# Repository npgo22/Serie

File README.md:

# Serie
Serie is a basic mainboard built to handle:
1. Insanely high temperatures
2. Insanely high speeds
3. Several axis of movement

The board itself is based around an STM32H723, the fastest microcontroller supported by Klipper at the moment.

## I/O
Currently, the following I/O is planned:

### Temperature sensing
Four MAX31856 (for type-k thermocouples) modules will be integrated for temperature sensing to be used as follows:
1. Hotend
2. Bed
3. Chamber
4. Spare/standby

Several other standard thermistor inputs will be broken out as needed.

### Motors
There will be 6x motors driven by TMC2241s. Each TMC2241 Support to klipper will need to be added to support this.

### Isolated Inputs
There are 16 digitally isolated inputs.

### Low Power Outputs
There are 6 outputs driven by small MOSFETs for outputs to other devices.

### Buses
As many buses should be broken out as possible.

### 12V Outputs
There are four 12V outputs to drive peripherals such as fans.

### USB
There will be at least 1 USB-C input.

### Ethernet
As I have ethernet stuff on hand, this board will have ethernet.

### Piezo Inputs
There will be a transimpedance amplifier followed by an instrumentation amplifier and an external comparator for piezo measurement. This is because the beacon probe cannot handle higher temperatures.

### Endstops
The enstops will utilize optoisolated inputs, and will be 3 pins to accomodate hall effect sensors.

## Power
As of right now, it is planned to require an external 48V power supply for the motors and a 12V power supply for the mainboard. This maintains galvanic isolation while providing decent protection against  A small switching regulator will generate 5V (AP62300TWU-7 + ETQP4M3R3KVK) which will then be fed into a 2112K-3.3.

### Heaters
Bed and chamber will be mains-powered, and motors will see 48V to 60V. and all the fans will maintain 12V, and the hotend heater cartridge will be able to handle 24V but will require a separate power supply just for it.

#### Switching
Mains powered items will be driven by an SSR, which necessitates the selection of a decent gate driver.

### Motors
Motors will be powered by a separate 48V power supply as they are extremely noisy.

## Board construction
Probably 4 layers. Don't really need more at this time.

## Misc.
* Consider a standardized header for breaking out to other boards.
* Total BoM cost for 2x is expected to be in the neighborhood of $150 once it's all assembled.

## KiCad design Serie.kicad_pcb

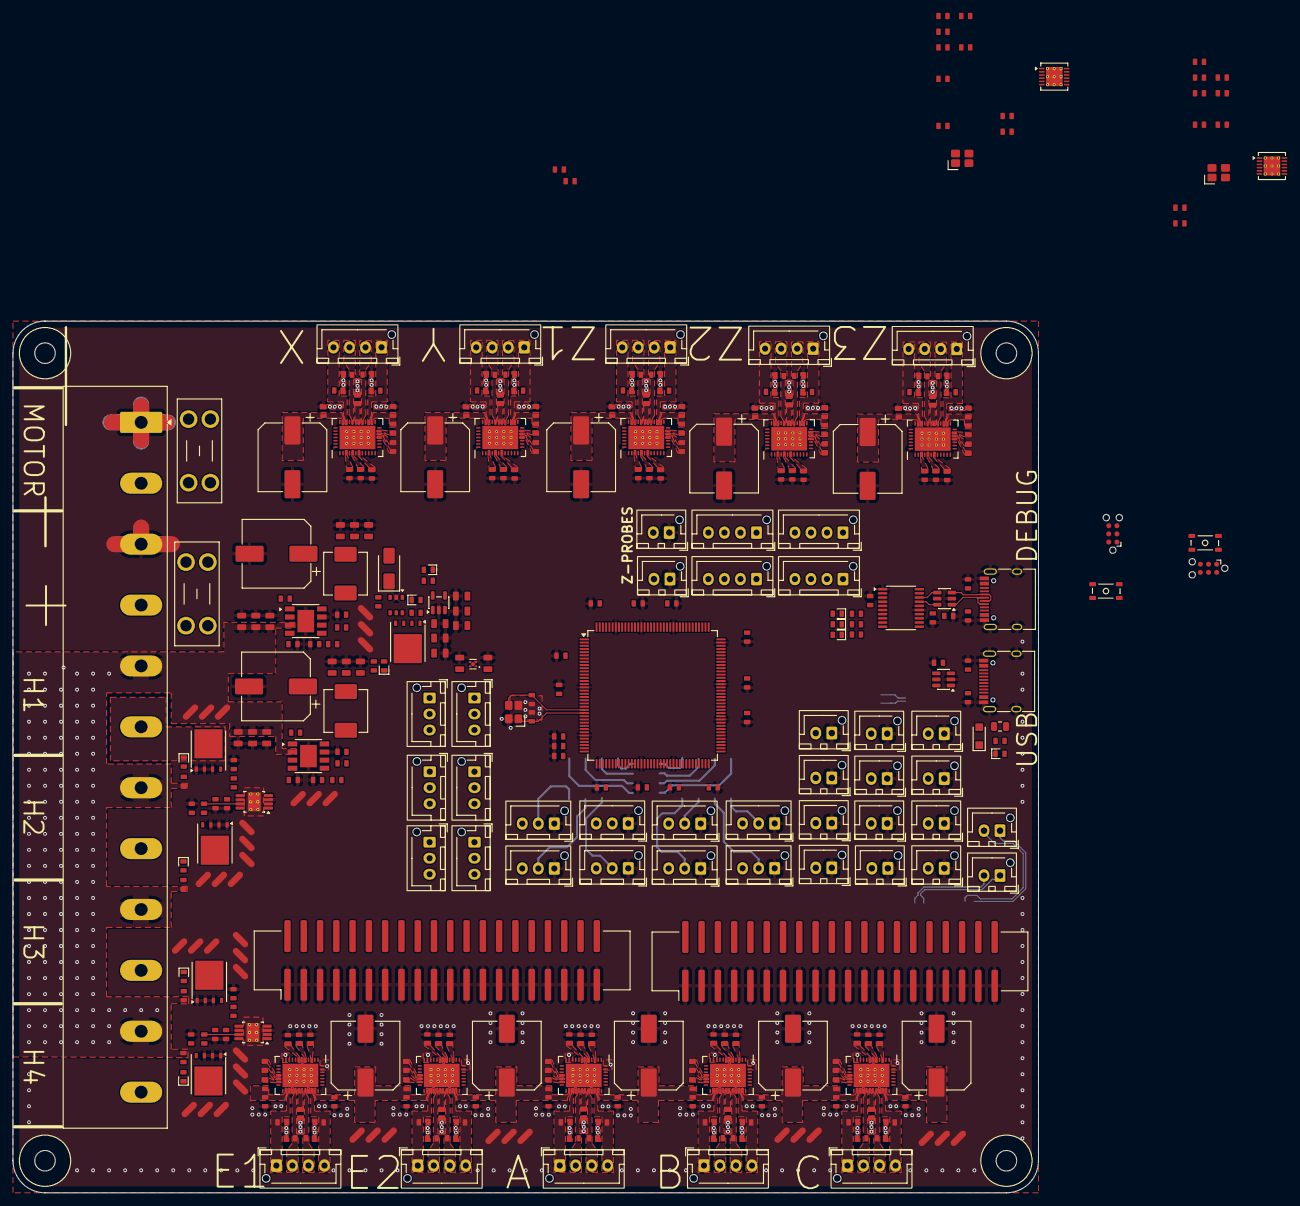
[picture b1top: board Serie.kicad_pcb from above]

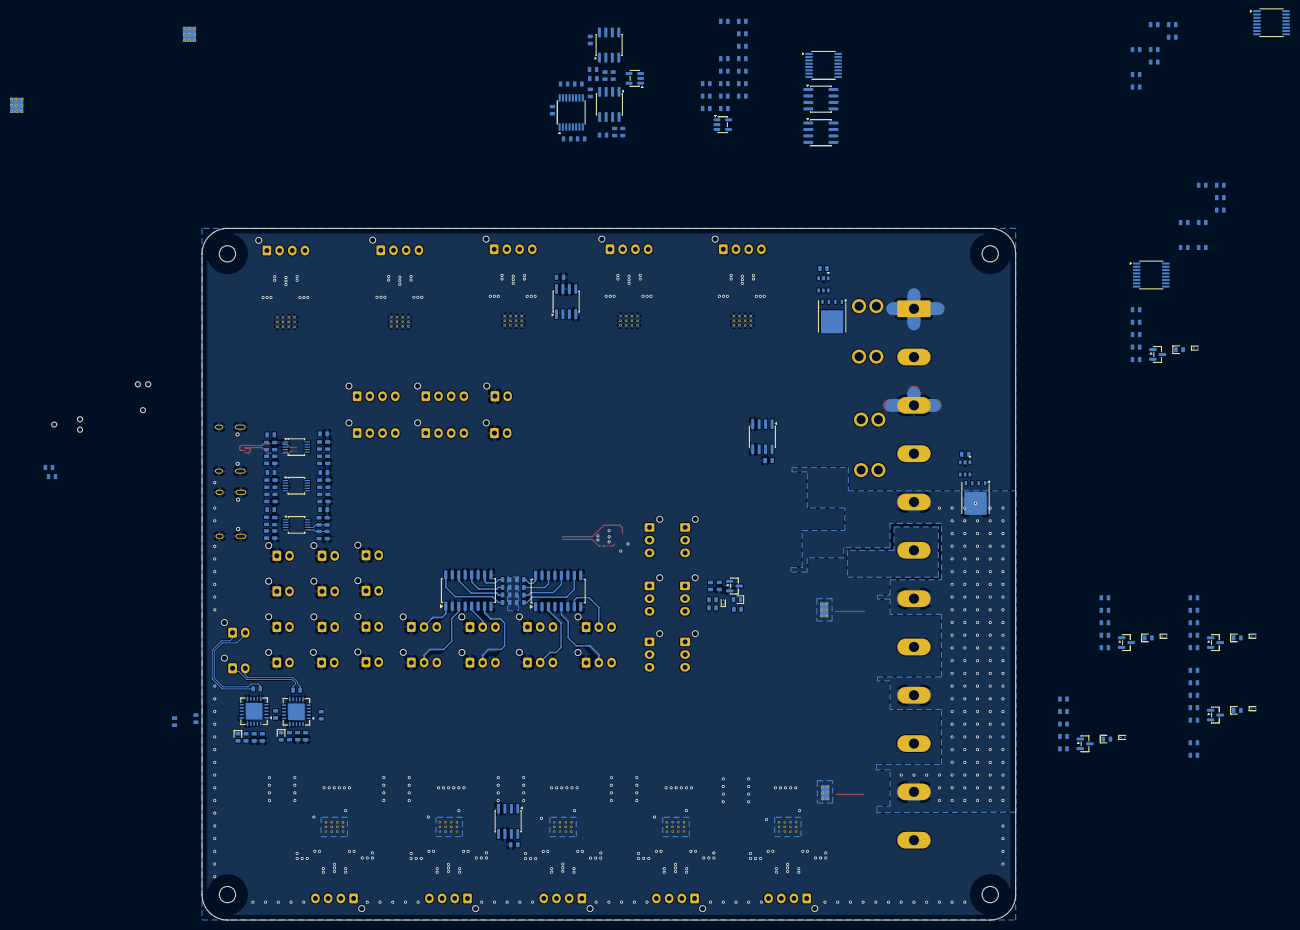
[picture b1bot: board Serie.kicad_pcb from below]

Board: 6 copper layers, 160.0 x 136.0 mm, 518 parts (179 on the bottom side), 303 nets.

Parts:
C1, C2: 10pF; C_0603
C3, C4, C93, C105, C117, C129, C141, C153, C184, C214, C226, C238: 2.2uF; C_0603
C5, C6, C7, C9, C12, C13, C14, C18, C19, C20, C21, C22, C24, C25, C26, C27, C28, C36, C38, C46, C56, C58, C59, C60, C61, C62, C63, C64, C65, C66, C67, C68, C69, C70, C71, C72, C74, C76, C77, C79, C80, C84, C85, C86, C92, C96, C97, C98, C104, C108, C109, C110, C116, C120, C121, C122, C128, C132, C133, C134, C140, C144, C145, C146, C152, C154, C155, C156, C158, C161, C162, C163, C167, C168, C169, C170, C171, C175, C176, C177, C183, C185, C186, C187, C188, C189, C191, C192, C193, C194, C195, C197, C198, C199, C200, C201, C205, C206, C207, C213, C217, C218, C219, C225, C229, C230, C231, C237: 100nF; C_0603
C8, C11, C78, C81, C157, C160: 10nF; C_0603
C10, C159: 10uF; C_0603
C15, C16, C164, C165: ?uF; C_0603
C17, C166: 100pF; C_0603
C23, C172: 30pF; C_0603
C29, C30, C31, C33, C34, C35, C39, C40, C41, C43, C44, C45, C48, C49, C50, C51, C52, C53, C54, C55: 22uF; C_0805
C32, C42, C87, C99, C111, C123, C135, C147, C178, C208, C220, C232: 100uF; CP_Elec_10x10.5
C37, C47: 1nF; C_0603
C57, C73, C75: 1uF; C_0603
C82, C83, C94, C95, C106, C107, C118, C119, C130, C131, C142, C143, C173, C174, C203, C204, C215, C216, C227, C228: 22nF; C_0603
C88, C89, C90, C91, C100, C101, C102, C103, C112, C113, C114, C115, C124, C125, C126, C127, C136, C137, C138, C139, C148, C149, C150, C151, C179, C180, C181, C182, C209, C210, C211, C212, C221, C222, C223, C224, C233, C234, C235, C236: 470pF; C_0603
C190, C196, C202: 100n; C_0603
D1: PMEG3010BER; Nexperia_CFP3_SOD-123W
D2, D3, D4, D5, D6, D8, D9, D10, D11, D12, D13, D14, D16, D18, D22, D24, D26: LED_Small; LED_0603
D7: SS54; D_SMA
D15, D17, D19, D23, D25, D27: ESD9B3.3ST5G; D_SOD-923
D20, D21: LED; LED_0603
F1: 500mA; Fuse_0805_2012Metric
F2, F3: XF-508P-B-B; Fuseholder_Blade_Mini_Keystone_3568
H1, H2, H3, H4: MountingHole; MountingHole_3.2mm_M3
J1, J2: Conn_02x20_Counter_Clockwise; IDC-Header_2x20_P2.54mm_Vertical_SMD
J3, J9: Conn_ARM_SWD_TagConnect_TC2030-NL; Tag-Connect_TC2030-IDC-NL_2x03_P1.27mm_Vertical
J4, J5, J24, J25, J26, J27, J28, J29, J30, J31, J33, J46, J47, J48: Conn_01x04; JST_XH_B4B-XH-AM_1x04_P2.50mm_Vertical
J6, J22, J23, J32, J34, J35, J36, J37, J38, J39, J40, J41, J42, J43, J44, J45: Conn_01x02; JST_XH_B2B-XH-AM_1x02_P2.50mm_Vertical
J7, J8: USB_C_Receptacle_USB2.0_16P; USB_C_Receptacle_HRO_TYPE-C-31-M-12
J10: Screw_Terminal_06x01x02; TerminalBlock_Ningbo-Kagnex_HB9500M_1x12_P9.5mm
J11, J12, J13, J14, J15, J16, J17, J18, J19, J20, J21, J49, J50, J51: Conn_01x03; JST_XH_B3B-XH-AM_1x03_P2.50mm_Vertical
L1: 6.8 uH; L_Changjiang_FXL0630
L2: 3.3 uH; L_Changjiang_FXL0630
Q1, Q2, Q3, Q4, Q5, Q6, Q7: BSC016N06NS; TDSON-8-1
Q8, Q9, Q10, Q11, Q12, Q13: AO3400A; SOT-23
R1, R2, R81, R82: 100R; R_0603
R3, R4, R5, R6, R7, R8, R9, R10, R16, R17, R21, R22, R48, R53, R58, R83, R84, R85, R86, R87, R88, R89, R90, R96, R97, R98, R99, R103, R104, R105, R106, R108, R109, R110, R111, R118, R123, R128: 4.7k; R_0603
R11, R36, R39, R42, R45, R50, R55, R60, R91, R120, R125, R130: 100k; R_0603
R12, R92: 10M; R_0603
R13, R14, R15, R18, R19, R20, R23, R25, R28, R31, R33, R34, R37, R40, R43, R46, R47, R51, R52, R56, R57, R61, R62, R63, R64, R65, R66, R67, R68, R69, R70, R72, R73, R93, R94, R100, R101, R102, R107, R112, R116, R117, R121, R122, R126, R127: 10k; R_0603
R24: 140k; R_0603
R26, R30: 200k; R_0603
R27, R32: 30.9k; R_0603
R29: 52.5k; R_0603
R35, R38, R41, R44, R49, R54, R59, R119, R124, R129: 10R; R_0603
R71, R74: 4.02k; R_0603
R75, R76, R77, R78, R79, R80, R95, R113, R114, R115: 24k; R_0603
SW1, SW2: SKRPANE010
U1: STM32H723ZGT6; LQFP-144_20x20mm_P0.5mm
U2, U30: ADS1220xPW; TSSOP-16_4.4x5mm_P0.65mm
U3, U31: TMUX1108PW; TSSOP-16_4.4x5mm_P0.65mm
U4, U5, U32, U33: TLV6742; SOIC-8_3.9x4.9mm_P1.27mm
U6, U34: LDC1612; WSON-12-1EP_4x4mm_P0.5mm_EP2.6x3mm_ThermalVias
U7, U35: TMUX1101DBV; SOT-23-5
U8, U10: USBLC6-2SC6; SOT-23-6
U9: STM32F042F4Px; TSSOP-20_4.4x6.5mm_P0.65mm
U11, U13: AP64500; Diodes_SO-8EP
U12, U14, U17: AP74700Q; SOT-6
U15: TLV77533; SOT-23-5
U16: TPS7A20xxxDQN; Texas_X2SON-4_1x1mm_P0.65mm
U18, U19: UCC27524DGN; Texas_DGN0008G_VSSOP-8-1EP_3x3mm_P0.65mm_EP2x2.94mm_Mask1.8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
U20, U21: LTV-247; SOP-16_4.4x10.4mm_P1.27mm
U22, U23: MAX31865xTP; TQFN-20-1EP_5x5mm_P0.65mm_EP3.25x3.25mm
U24, U25, U26, U27, U28, U29, U36, U43, U44, U45: TMC2241ATC; QFN-38_EP_5.63x7.6_Pitch0.5mm
U37, U39, U42: ADS1115IDGS; TSSOP-10_3x3mm_P0.5mm
U38, U40, U41: LM75B; SOIC-8_3.9x4.9mm_P1.27mm
Y1: 25 MHz; 3225-4P-L
Y2, Y3: 12 MHz; 3225-4P-L

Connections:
+3.3V: C5.2, C7.2, C12.2, C13.2, C14.1, C22.1, C24.1, C25.1, C51.2, C52.2, C53.2, C57.2, C58.2, C59.2, C60.2, C61.2, C62.2, C63.2, C64.2, C65.2, C66.2, C67.2, C68.2, C69.2, C70.2, C71.2, C76.1, C77.1, C79.1, C80.1, C92.2, C104.2, C116.2, C128.2, C140.2, C152.2, C154.2, C156.2, C161.2, C162.2, C163.1, C171.1, C183.2, C185.1, C186.1, C191.1, C192.1, C197.1, C198.1, C213.2, C225.2, C237.2, D3.2 (A), D4.2 (A), D5.2 (A), J3.1 (VCC), J9.1 (VCC), J14.3, J15.3, J16.3, J17.3, J18.3, J19.3, J20.3, J21.3, R13.1, R33.1, R46.1, R51.1, R56.1, R61.1, R62.1, R63.1, R64.1, R65.1, R66.1, R67.1, R68.1, R69.1, R70.1, R72.1, R73.1, R93.1, R96.1, R97.1, R98.1, R99.1, R100.2, R101.2, R102.2, R103.1, R104.1, R105.1, R106.1, R107.2, R108.1, R109.1, R110.1, R111.1, R112.2, R116.1, R121.1, R126.1, U1.6 (VBAT), U1.17 (VDD), U1.30 (VDD), U1.32 (VREF+), U1.33 (VDDA), U1.39 (VDD), U1.52 (VDD), U1.62 (VDD), U1.72 (VDD), U1.84 (VDD), U1.95 (VDD33USB), U1.108 (VDD), U1.121 (VDD), U1.131 (VDD), U1.143 (PDR_ON), U1.144 (VDD), U2.13 (DVDD), U3.2 (EN), U3.13 (VDD), U4.8 (V+), U5.8 (V+), U6.7 (VDD), U7.5 (V_{DD}), U9.5 (VDDA), U9.16 (VDD), U15.5 (VOUT), U22.19 (DVDD), U22.20 (VDD), U23.19 (DVDD), U23.20 (VDD), U24.7 (VCCIO), U24.33 (~SLEEP), U25.7 (VCCIO), U25.33 (~SLEEP), U26.7 (VCCIO), U26.33 (~SLEEP), U27.7 (VCCIO), U27.33 (~SLEEP), U28.7 (VCCIO), U28.33 (~SLEEP), U29.7 (VCCIO), U29.33 (~SLEEP), U30.13 (DVDD), U31.2 (EN), U31.13 (VDD), U32.8 (V+), U33.8 (V+), U34.7 (VDD), U35.5 (V_{DD}), U36.7 (VCCIO), U36.33 (~SLEEP), U37.8 (VDD), U38.6 (A1), U38.7 (A0), U38.8 (+Vs), U39.1 (ADDR), U39.8 (VDD), U40.5 (A2), U40.8 (+Vs), U41.5 (A2), U41.7 (A0), U41.8 (+Vs), U42.8 (VDD), U43.7 (VCCIO), U43.33 (~SLEEP), U44.7 (VCCIO), U44.33 (~SLEEP), U45.7 (VCCIO), U45.33 (~SLEEP), Y2.4 (V+), Y3.4 (V+)
+4.5V: C6.1, C10.1, C55.1, C155.1, C159.1, J4.4, J30.4, U2.11 (AIN0/REFP1), U2.12 (AVDD), U16.1 (OUT), U30.11 (AIN0/REFP1), U30.12 (AVDD)
+5V: C48.2, C49.2, C50.2, C54.1, D1.1 (K), Q2.5 (D), U14.4 (CATHODE), U15.1 (VIN), U15.3 (EN), U16.3 (EN), U16.4 (IN)
+12V: C32.1, C33.1, C34.1, C35.1, C72.2, C73.2, C74.2, C75.2, J11.1, J12.1, J13.1, J49.1, J50.1, J51.1, L1.2, R23.1, R24.1, R47.1, R52.1, R57.1, R117.1, R122.1, R127.1, U18.1 (ENA), U18.6 (V_{DD}), U18.8 (ENB), U19.1 (ENA), U19.6 (V_{DD}), U19.8 (ENB)
+24V: C29.1, C30.1, C31.1, C39.1, C40.1, C41.1, J10.5 (Pin_1), J10.7 (Pin_1), J10.9 (Pin_1), J10.11 (Pin_1), Q1.5 (D), R34.1, R37.1, R40.1, R43.1, U11.2 (VIN), U11.3 (EN), U12.4 (CATHODE), U13.2 (VIN), U13.3 (EN)
/Connections/Debugger and USB/IF_SWCLK: J9.4 (SWCLK), U9.20 (PA14)
/Connections/Debugger and USB/IF_SWDIO: J9.2 (SWDIO), U9.19 (PA13)
/Connections/Debugger and USB/USB_CONN_D+: J7.A6 (D+), J7.B6 (D+), J8.A6 (D+), J8.B6 (D+), U8.3 (I/O2), U10.3 (I/O2)
/Connections/Debugger and USB/USB_CONN_D-: J7.A7 (D-), J7.B7 (D-), J8.A7 (D-), J8.B7 (D-), U8.1 (I/O1), U10.1 (I/O1)
/Connections/Debugger and USB/USB_D+: U9.18 (PA10/PA12), U10.4 (I/O2)
/Connections/Debugger and USB/USB_D-: U9.17 (PA9/PA11), U10.6 (I/O1)
/Connections/Debugger and USB/~RST: J9.3 (~RESET), SW2.3 (K), SW2.4 (A), U9.4 (NRST)
/Connections/High Power Outputs 1/OUTA: R35.1, U18.5 (OUTB)
/Connections/High Power Outputs 1/OUTB: R38.1, U18.7 (OUTA)
/Connections/High Power Outputs 2/OUTA: R41.1, U19.5 (OUTB)
/Connections/High Power Outputs 2/OUTB: R44.1, U19.7 (OUTA)
/Connections/IN1: R61.2, U20.16
/Connections/IN2: R62.2, U20.14
/Connections/IN3: R63.2, U20.12
/Connections/IN4: R64.2, U20.10
/Connections/IN5: R65.2, U21.16
/Connections/IN6: R66.2, U21.14
/Connections/IN7: R67.2, U21.12
/Connections/IN8: R68.2, U21.10
/Connections/Low Power Outputs/TACH1: D15.2 (A2), R46.2, R48.2
/Connections/Low Power Outputs/TACH2: D17.2 (A2), R51.2, R53.2
/Connections/Low Power Outputs/TACH3: D19.2 (A2), R56.2, R58.2
/Connections/Low Power Outputs/TACH4: D23.2 (A2), R116.2, R118.2
/Connections/Low Power Outputs/TACH5: D25.2 (A2), R121.2, R123.2
/Connections/Low Power Outputs/TACH6: D27.2 (A2), R126.2, R128.2
/Connections/SWCLK: J3.4 (SWCLK), U1.109 (PA14(JTCK), U9.12 (PA6)
/Connections/SWDIO: J3.2 (SWDIO), U1.105 (PA13(JTMS), U9.11 (PA5)
/Connections/Sensors 1/CLK: C23.1, U6.3 (CLKIN), Y2.3 (OUT)
/Connections/Sensors 1/PIEZO: U5.6 (-), U5.7
/Connections/Sensors 1/vref: U3.8 (D), U4.3 (+), U4.7
/Connections/Sensors 2/CLK: C172.1, U34.3 (CLKIN), Y3.3 (OUT)
/Connections/Sensors 2/PIEZO: U33.6 (-), U33.7
/Connections/Sensors 2/vref: U31.8 (D), U32.3 (+), U32.7
/Connections/Thermistors/SCL: R101.1, U37.10 (SCL), U38.2 (SCL), U39.10 (SCL), U40.2 (SCL), U41.2 (SCL), U42.10 (SCL)
/Connections/Thermistors/SDA: R102.1, U37.9 (SDA), U38.1 (SDA), U39.9 (SDA), U40.1 (SDA), U41.1 (SDA), U42.1 (ADDR), U42.9 (SDA)
/Connections/Thermistors/TS_ALRT/RDY_1: R100.1, U37.2 (ALERT/RDY)
/Connections/Thermistors/TS_ALRT/RDY_2: R107.1, U39.2 (ALERT/RDY)
/Connections/Thermistors/TS_ALRT/RDY_3: R112.1, U42.2 (ALERT/RDY)
/Connections/Thermocouple 1/T1+: C78.1, J22.2, U22.5 (FORCE+), U22.7 (RTDIN+)
/Connections/Thermocouple 1/T1-: C78.2, J22.1, U22.8 (RTDIN-), U22.9 (FORCE-)
/Connections/Thermocouple 2/T1+: C81.1, J23.2, U23.5 (FORCE+), U23.7 (RTDIN+)
/Connections/Thermocouple 2/T1-: C81.2, J23.1, U23.8 (RTDIN-), U23.9 (FORCE-)
/Connections/~RST: J3.3 (~RESET), SW1.1, SW1.2, U1.25 (NRST), U9.14 (PB1)
/Connections/~TC_CS_1: R70.2, U22.13 (~CS)
/Connections/~TC_CS_2: R73.2, U23.13 (~CS)
DRV_MISO: U24.37 (SDO/NAO), U25.37 (SDO/NAO), U26.37 (SDO/NAO), U27.37 (SDO/NAO), U28.37 (SDO/NAO), U29.37 (SDO/NAO), U36.37 (SDO/NAO), U43.37 (SDO/NAO), U44.37 (SDO/NAO), U45.37 (SDO/NAO)
DRV_MOSI: U24.36 (SDI/AD0), U25.36 (SDI/AD0), U26.36 (SDI/AD0), U27.36 (SDI/AD0), U28.36 (SDI/AD0), U29.36 (SDI/AD0), U36.36 (SDI/AD0), U43.36 (SDI/AD0), U44.36 (SDI/AD0), U45.36 (SDI/AD0)
DRV_SCK: U24.35 (SCK/AD1), U25.35 (SCK/AD1), U26.35 (SCK/AD1), U27.35 (SCK/AD1), U28.35 (SCK/AD1), U29.35 (SCK/AD1), U36.35 (SCK/AD1), U43.35 (SCK/AD1), U44.35 (SCK/AD1), U45.35 (SCK/AD1)
GND: C1.1, C2.1, C3.1, C4.1, C5.1, C6.2, C7.1, C8.1, C11.2, C12.1, C13.1, C14.2, C18.1, C19.1, C20.1, C21.1, C22.2, C23.2, C24.2, C25.2, C26.2, C27.2, C29.2, C30.2, C31.2, C32.2, C33.2, C34.2, C35.2, C37.2, C39.2, C40.2, C41.2, C42.2, C43.2, C44.2, C45.2, C47.2, C48.1, C49.1, C50.1, C51.1, C52.1, C53.1, C54.2, C55.2, C57.1, C58.1, C59.1, C60.1, C61.1, C62.1, C63.1, C64.1, C65.1, C66.1, C67.1, C68.1, C69.1, C70.1, C71.1, C72.1, C73.1, C74.1, C75.1, C76.2, C77.2, C79.2, C80.2, C84.2, C85.2, C86.2, C87.2, C88.2, C89.2, C90.2, C91.2, C92.1, C93.1, C96.2, C97.2, C98.2, C99.2, C100.2, C101.2, C102.2, C103.2, C104.1, C105.1, C108.2, C109.2, C110.2, C111.2, C112.2, C113.2, C114.2, C115.2, C116.1, C117.1, C120.2, C121.2, C122.2, C123.2, C124.2, C125.2, C126.2, C127.2, C128.1, C129.1, C132.2, C133.2, C134.2, C135.2, C136.2, C137.2, C138.2, C139.2, C140.1, C141.1, C144.2, C145.2, C146.2, C147.2, C148.2, C149.2, C150.2, C151.2, C152.1, C153.1, C154.1, C155.2, C156.1, C157.1, C160.2, C161.1, C162.1, C163.2, C167.1, C168.1, C169.1, C170.1, C171.2, C172.2, C175.2, C176.2, C177.2, C178.2, C179.2, C180.2, C181.2, C182.2, C183.1, C184.1, C185.2, C186.2, C187.1, C188.1, C189.1, C190.1, C191.2, C192.2, C193.1, C194.1, C195.1, C196.1, C197.2, C198.2, C199.1, C200.1, C201.1, C202.1, C205.2, C206.2, C207.2, C208.2, C209.2, C210.2, C211.2, C212.2, C213.1, C214.1, C217.2, C218.2, C219.2, C220.2, C221.2, C222.2, C223.2, C224.2, C225.1, C226.1, C229.2, C230.2, C231.2, C232.2, C233.2, C234.2, C235.2, C236.2, C237.1, C238.1, D2.1 (K), D6.1 (K), D8.1 (K), D9.1 (K), D15.1 (A1), D17.1 (A1), D19.1 (A1), D23.1 (A1), D25.1 (A1), D27.1 (A1), J1.1, J1.3, J1.5, J1.7, J1.9, J1.11, J1.13, J1.15, J1.17, J1.19, J1.21, J1.23, J1.25, J1.27, J1.29, J1.31, J1.33, J1.35, J1.37, J1.39, J2.1, J2.3, J2.5, J2.7, J2.9, J2.11, J2.13, J2.15, J2.17, J2.19, J2.21, J2.23, J2.25, J2.27, J2.29, J2.31, J2.33, J2.35, J2.37, J2.39, J3.5 (GND), J6.1, J7.A1 (GND), J7.A12 (GND), J7.B1 (GND), J7.B12 (GND), J7.S1 (SHIELD), J8.A1 (GND), J8.A12 (GND), J8.B1 (GND), J8.B12 (GND), J8.S1 (SHIELD), J9.5 (GND), J10.1, J10.3 (Pin_1), J14.1, J15.1, J16.1, J17.1, J18.1, J19.1, J20.1, J21.1, J32.1, J34.1, J35.1, J36.1, J37.1, J38.1, J39.1, J40.1, J41.1, J42.1, J43.1, J44.1, J45.1, Q4.1 (S), Q4.2 (S), Q4.3 (S), Q5.1 (S), Q5.2 (S), Q5.3 (S), Q6.1 (S), Q6.2 (S), Q6.3 (S), Q7.1 (S), Q7.2 (S), Q7.3 (S), Q8.2 (S), Q9.2 (S), Q10.2 (S), Q11.2 (S), Q12.2 (S), Q13.2 (S), R14.1, R16.1, R17.2, R21.1, R22.2, R25.2, R26.2, R30.2, R31.2, R36.1, R39.1, R42.1, R45.1, R50.1, R55.1, R60.1, R75.2, R76.2, R77.2, R78.2, R79.2, R80.2, R94.1, R95.2, R113.2, R114.2, R115.2, R120.1, R125.1, R130.1, SW1.3 (K), SW1.4 (A), SW2.1, SW2.2, U1.16 (VSS), U1.31 (VSSA), U1.38 (VSS), U1.51 (VSS), U1.61 (VSS), U1.83 (VSS), U1.94 (VSS), U1.107 (VSS), U1.120 (VSS), U1.130 (VSS), U1.138 (BOOT0), U2.3 (CLK), U2.4 (DGND), U2.5 (AVSS), U3.3 (VSS), U3.14 (GND), U4.4 (V-), U4.5 (+), U5.4 (V-), U6.4 (ADDR), U6.6 (SD), U6.8 (GND), U6.13 (GND), U7.2, U7.3 (GND), U8.2 (GND), U9.1 (PB8), U9.15 (VSSA), U10.2 (GND), U11.7 (GND), U11.9 (EP), U12.2 (GND), U13.7 (GND), U13.9 (EP), U14.2 (GND), U15.2 (GND), U16.2 (GND), U16.5 (Pad), U17.2 (GND), U18.3 (GND), U18.9 (GND), U19.3 (GND), U19.9 (GND), U20.2, U20.4, U20.6, U20.8, U20.9, U20.11, U20.13, U20.15, U21.2, U21.4, U21.6, U21.8, U21.9, U21.11, U21.13, U21.15, U22.6 (FORCE2), U22.10 (GND), U22.15 (DGND), U22.16 (GND), U22.21 (GND), U23.6 (FORCE2), U23.10 (GND), U23.15 (DGND), U23.16 (GND), U23.21 (GND), U24.6 (AGND), U24.11 (DRV_EN), U24.23 (PGND), U24.28 (PGND), U24.38 (CLK), U24.39 (EP), U25.6 (AGND), U25.11 (DRV_EN), U25.23 (PGND), U25.28 (PGND), U25.38 (CLK), U25.39 (EP), U26.6 (AGND), U26.11 (DRV_EN), U26.23 (PGND), U26.28 (PGND), U26.38 (CLK), U26.39 (EP), U27.6 (AGND), U27.11 (DRV_EN), U27.23 (PGND), U27.28 (PGND), U27.38 (CLK), U27.39 (EP), U28.6 (AGND), U28.11 (DRV_EN), U28.23 (PGND), U28.28 (PGND), U28.38 (CLK), U28.39 (EP), U29.6 (AGND), U29.11 (DRV_EN), U29.23 (PGND), U29.28 (PGND), U29.38 (CLK), U29.39 (EP), U30.3 (CLK), U30.4 (DGND), U30.5 (AVSS), U31.3 (VSS), U31.14 (GND), U32.4 (V-), U32.5 (+), U33.4 (V-), U34.4 (ADDR), U34.6 (SD), U34.8 (GND), U34.13 (GND), U35.2, U35.3 (GND), U36.6 (AGND), U36.11 (DRV_EN), U36.23 (PGND), U36.28 (PGND), U36.38 (CLK), U36.39 (EP), U37.1 (ADDR), U37.3 (GND), U38.4 (GND), U38.5 (A2), U39.3 (GND), U40.4 (GND), U40.6 (A1), U40.7 (A0), U41.4 (GND), U41.6 (A1), U42.3 (GND), U43.6 (AGND), U43.11 (DRV_EN), U43.23 (PGND), U43.28 (PGND), U43.38 (CLK), U43.39 (EP), U44.6 (AGND), U44.11 (DRV_EN), U44.23 (PGND), U44.28 (PGND), U44.38 (CLK), U44.39 (EP), U45.6 (AGND), U45.11 (DRV_EN), U45.23 (PGND), U45.28 (PGND), U45.38 (CLK), U45.39 (EP), Y1.2 (G), Y1.4 (G), Y2.2 (GND), Y3.2 (GND)
MCU_USB_D+: U1.104 (PA12), U8.4 (I/O2)
MCU_USB_D-: U1.103 (PA11), U8.6 (I/O1)
unnamed: C3.2, U1.71 (VCAP)
unnamed: C4.2, U1.106 (VCAP)
unnamed: C37.1, R27.2
unnamed: C47.1, R32.2
unnamed: D1.2 (A), F1.2, R15.1
unnamed: D2.2 (A), R15.2
unnamed: D3.1 (K), R18.1
unnamed: D4.1 (K), R19.1
unnamed: D5.1 (K), R20.1
unnamed: D6.2 (A), R23.2
unnamed: C42.1, C43.1, C44.1, C45.1, D7.2 (A), L2.2
unnamed: C46.2, D7.1 (K), Q2.1 (S), Q2.2 (S), Q2.3 (S), R28.1, R29.1, U14.3 (EN), U14.6 (ANODE)
unnamed: D8.2 (A), R28.2
unnamed: D9.2 (A), R33.2
unnamed: D10.2 (A), R34.2
unnamed: D10.1 (K), J10.6 (Pin_2), Q4.5 (D)
unnamed: D11.2 (A), R37.2
unnamed: D11.1 (K), J10.8 (Pin_2), Q5.5 (D)
unnamed: D12.2 (A), R40.2
unnamed: D12.1 (K), J10.10 (Pin_2), Q6.5 (D)
unnamed: D13.2 (A), R43.2
unnamed: D13.1 (K), J10.12 (Pin_2), Q7.5 (D)
unnamed: D14.2 (A), R47.2
unnamed: D14.1 (K), J11.2, Q8.3 (D)
unnamed: D16.2 (A), R52.2
unnamed: D16.1 (K), J12.2, Q9.3 (D)
unnamed: D18.2 (A), R57.2
unnamed: D18.1 (K), J13.2, Q10.3 (D)
unnamed: D20.2 (A), R69.2
unnamed: D20.1 (K), U22.18 (~DRDY)
unnamed: D21.2 (A), R72.2
unnamed: D21.1 (K), U23.18 (~DRDY)
unnamed: D22.2 (A), R117.2
unnamed: D22.1 (K), J49.2, Q11.3 (D)
unnamed: D24.2 (A), R122.2
unnamed: D24.1 (K), J50.2, Q12.3 (D)
unnamed: D26.2 (A), R127.2
unnamed: D26.1 (K), J51.2, Q13.3 (D)
unnamed: F2.1, Q1.1 (S), Q1.2 (S), Q1.3 (S)
unnamed: C10.2, J4.1, U2.6 (AIN3/REFN1)
unnamed: J4.2, R2.1
unnamed: J4.3, R1.1
unnamed: C16.1, C21.2, J5.1, U6.12 (IN1B)
unnamed: C16.2, C20.2, J5.2, U6.11 (IN1A)
unnamed: C15.1, C19.2, J5.3, U6.10 (IN0B)
unnamed: C15.2, C18.2, J5.4, U6.9 (IN0A)
unnamed: C17.1, J6.2, R12.1, U4.2 (-), U7.1
unnamed: J7.A5 (CC1), R17.1
unnamed: J7.B5 (CC2), R16.2
unnamed: J8.A5 (CC1), R22.1
unnamed: J8.B5 (CC2), R21.2
unnamed: F3.2, J10.2
unnamed: C36.2, F2.2, J10.4 (Pin_2), U12.3 (EN), U12.6 (ANODE)
unnamed: J11.3, R48.1
unnamed: J12.3, R53.1
unnamed: J13.3, R58.1
unnamed: J14.2, U20.1
unnamed: J15.2, U20.3
unnamed: J16.2, U20.5
unnamed: J17.2, U20.7
unnamed: J18.2, U21.1
unnamed: J19.2, U21.3
unnamed: J20.2, U21.5
unnamed: J21.2, U21.7
unnamed: C91.1, J24.1, U24.22 (OUT1B)
unnamed: C90.1, J24.2, U24.24 (OUT2B)
unnamed: C88.1, J24.3, U24.27 (OUT2A)
unnamed: C89.1, J24.4, U24.29 (OUT1A)
unnamed: C103.1, J25.1, U25.22 (OUT1B)
unnamed: C102.1, J25.2, U25.24 (OUT2B)
unnamed: C100.1, J25.3, U25.27 (OUT2A)
unnamed: C101.1, J25.4, U25.29 (OUT1A)
unnamed: C115.1, J26.1, U26.22 (OUT1B)
unnamed: C114.1, J26.2, U26.24 (OUT2B)
unnamed: C112.1, J26.3, U26.27 (OUT2A)
unnamed: C113.1, J26.4, U26.29 (OUT1A)
unnamed: C127.1, J27.1, U27.22 (OUT1B)
unnamed: C126.1, J27.2, U27.24 (OUT2B)
unnamed: C124.1, J27.3, U27.27 (OUT2A)
unnamed: C125.1, J27.4, U27.29 (OUT1A)
unnamed: C139.1, J28.1, U28.22 (OUT1B)
unnamed: C138.1, J28.2, U28.24 (OUT2B)
unnamed: C136.1, J28.3, U28.27 (OUT2A)
unnamed: C137.1, J28.4, U28.29 (OUT1A)
unnamed: C151.1, J29.1, U29.22 (OUT1B)
unnamed: C150.1, J29.2, U29.24 (OUT2B)
unnamed: C148.1, J29.3, U29.27 (OUT2A)
unnamed: C149.1, J29.4, U29.29 (OUT1A)
unnamed: C159.2, J30.1, U30.6 (AIN3/REFN1)
unnamed: J30.2, R82.1
unnamed: J30.3, R81.1
unnamed: C165.1, C170.2, J31.1, U34.12 (IN1B)
unnamed: C165.2, C169.2, J31.2, U34.11 (IN1A)
unnamed: C164.1, C168.2, J31.3, U34.10 (IN0B)
unnamed: C164.2, C167.2, J31.4, U34.9 (IN0A)
unnamed: C166.1, J32.2, R92.1, U32.2 (-), U35.1
unnamed: C182.1, J33.1, U36.22 (OUT1B)
unnamed: C181.1, J33.2, U36.24 (OUT2B)
unnamed: C179.1, J33.3, U36.27 (OUT2A)
unnamed: C180.1, J33.4, U36.29 (OUT1A)
unnamed: C187.2, J34.2, R96.2, U37.4 (AIN0)
unnamed: C188.2, J35.2, R97.2, U37.5 (AIN1)
unnamed: C189.2, J36.2, R98.2, U37.6 (AIN2)
unnamed: C190.2, J37.2, R99.2, U37.7 (AIN3)
unnamed: C193.2, J38.2, R103.2, U39.4 (AIN0)
unnamed: C194.2, J39.2, R104.2, U39.5 (AIN1)
unnamed: C195.2, J40.2, R105.2, U39.6 (AIN2)
unnamed: C196.2, J41.2, R106.2, U39.7 (AIN3)
unnamed: C199.2, J42.2, R108.2, U42.4 (AIN0)
unnamed: C200.2, J43.2, R109.2, U42.5 (AIN1)
unnamed: C201.2, J44.2, R110.2, U42.6 (AIN2)
unnamed: C202.2, J45.2, R111.2, U42.7 (AIN3)
unnamed: C212.1, J46.1, U43.22 (OUT1B)
unnamed: C211.1, J46.2, U43.24 (OUT2B)
unnamed: C209.1, J46.3, U43.27 (OUT2A)
unnamed: C210.1, J46.4, U43.29 (OUT1A)
unnamed: C224.1, J47.1, U44.22 (OUT1B)
unnamed: C223.1, J47.2, U44.24 (OUT2B)
unnamed: C221.1, J47.3, U44.27 (OUT2A)
unnamed: C222.1, J47.4, U44.29 (OUT1A)
unnamed: C236.1, J48.1, U45.22 (OUT1B)
unnamed: C235.1, J48.2, U45.24 (OUT2B)
unnamed: C233.1, J48.3, U45.27 (OUT2A)
unnamed: C234.1, J48.4, U45.29 (OUT1A)
unnamed: J49.3, R118.1
unnamed: J50.3, R123.1
unnamed: J51.3, R128.1
unnamed: Q1.4 (G), U12.5 (GATE)
unnamed: Q2.4 (G), U14.5 (GATE)
unnamed: Q3.4 (G), U17.5 (GATE)
unnamed: Q4.4 (G), R35.2, R36.2
unnamed: Q5.4 (G), R38.2, R39.2
unnamed: Q6.4 (G), R41.2, R42.2
unnamed: Q7.4 (G), R44.2, R45.2
unnamed: Q8.1 (G), R49.2, R50.2
unnamed: Q9.1 (G), R54.2, R55.2
unnamed: Q10.1 (G), R59.2, R60.2
unnamed: Q11.1 (G), R119.2, R120.2
unnamed: Q12.1 (G), R124.2, R125.2
unnamed: Q13.1 (G), R129.2, R130.2
unnamed: C2.2, U1.23 (PH0), Y1.3
unnamed: C1.2, U1.24 (PH1), Y1.1
unnamed: C8.2, C9.1, R1.2, U2.10 (AIN1)
unnamed: C9.2, C11.1, R2.2, U2.7 (AIN2)
unnamed: R3.1, U3.4 (S1)
unnamed: R3.2, R4.1, U3.5 (S2)
unnamed: R4.2, R5.1, U3.6 (S3)
unnamed: R5.2, R6.1, U3.7 (S4)
unnamed: R6.2, R7.1, U3.12 (S5)
unnamed: R7.2, R8.1, U3.11 (S6)
unnamed: R8.2, R9.1, U3.10 (S7)
unnamed: R9.2, R10.1, U3.9 (S8)
unnamed: R13.2, R14.2, U4.6 (-)
unnamed: C17.2, R12.2, U4.1, U5.3 (+)
unnamed: R11.1, U5.2 (-)
unnamed: R10.2, R11.2, U5.1, U5.5 (+)
unnamed: C26.1, F1.1, J7.A4 (VBUS), J7.A9 (VBUS), J7.B4 (VBUS), J7.B9 (VBUS), U8.5 (VBUS)
unnamed: R18.2, U9.6 (PA0)
unnamed: R19.2, U9.7 (PA1)
unnamed: R20.2, U9.10 (PA4)
unnamed: C27.1, J8.A4 (VBUS), J8.A9 (VBUS), J8.B4 (VBUS), J8.B9 (VBUS), U10.5 (VBUS)
unnamed: C28.2, U11.1 (BST)
unnamed: R27.1, U11.6 (COMP)
unnamed: R24.2, R25.1, U11.5 (FB)
unnamed: R26.1, U11.4 (RT/CLK)
unnamed: C28.1, L1.1, U11.8 (SW)
unnamed: C36.1, U12.1 (VCP)
unnamed: C38.2, U13.1 (BST)
unnamed: R32.1, U13.6 (COMP)
unnamed: R29.2, R31.1, U13.5 (FB)
unnamed: R30.1, U13.4 (RT/CLK)
unnamed: C38.1, L2.1, U13.8 (SW)
unnamed: C46.1, U14.1 (VCP)
unnamed: C56.2, F3.1, Q3.1 (S), Q3.2 (S), Q3.3 (S), U17.3 (EN), U17.6 (ANODE)
unnamed: C56.1, U17.1 (VCP)
unnamed: R71.1, U22.1 (BIAS), U22.2 (REFIN+)
unnamed: R71.2, U22.3 (REFIN-), U22.4 (ISENSOR)
unnamed: R74.1, U23.1 (BIAS), U23.2 (REFIN+)
unnamed: R74.2, U23.3 (REFIN-), U23.4 (ISENSOR)
unnamed: C82.2, U24.16 (CPI)
unnamed: C82.1, U24.17 (CPO)
unnamed: R75.1, U24.3 (IREF)
unnamed: C83.2, U24.18 (VCP)
unnamed: C93.2, U24.5 (VDD18)
unnamed: C94.2, U25.16 (CPI)
unnamed: C94.1, U25.17 (CPO)
unnamed: R76.1, U25.3 (IREF)
unnamed: C95.2, U25.18 (VCP)
unnamed: C105.2, U25.5 (VDD18)
unnamed: C106.2, U26.16 (CPI)
unnamed: C106.1, U26.17 (CPO)
unnamed: R77.1, U26.3 (IREF)
unnamed: C107.2, U26.18 (VCP)
unnamed: C117.2, U26.5 (VDD18)
unnamed: C118.2, U27.16 (CPI)
unnamed: C118.1, U27.17 (CPO)
unnamed: R78.1, U27.3 (IREF)
unnamed: C119.2, U27.18 (VCP)
unnamed: C129.2, U27.5 (VDD18)
unnamed: C130.2, U28.16 (CPI)
unnamed: C130.1, U28.17 (CPO)
unnamed: R79.1, U28.3 (IREF)
unnamed: C131.2, U28.18 (VCP)
unnamed: C141.2, U28.5 (VDD18)
unnamed: C142.2, U29.16 (CPI)
unnamed: C142.1, U29.17 (CPO)
unnamed: R80.1, U29.3 (IREF)
unnamed: C143.2, U29.18 (VCP)
unnamed: C153.2, U29.5 (VDD18)
unnamed: C157.2, C158.1, R81.2, U30.10 (AIN1)
unnamed: C158.2, C160.1, R82.2, U30.7 (AIN2)
unnamed: R83.1, U31.4 (S1)
unnamed: R83.2, R84.1, U31.5 (S2)
unnamed: R84.2, R85.1, U31.6 (S3)
unnamed: R85.2, R86.1, U31.7 (S4)
unnamed: R86.2, R87.1, U31.12 (S5)
unnamed: R87.2, R88.1, U31.11 (S6)
unnamed: R88.2, R89.1, U31.10 (S7)
unnamed: R89.2, R90.1, U31.9 (S8)
unnamed: R93.2, R94.2, U32.6 (-)
unnamed: C166.2, R92.2, U32.1, U33.3 (+)
unnamed: R91.1, U33.2 (-)
unnamed: R90.2, R91.2, U33.1, U33.5 (+)
unnamed: C173.2, U36.16 (CPI)
unnamed: C173.1, U36.17 (CPO)
unnamed: R95.1, U36.3 (IREF)
unnamed: C174.2, U36.18 (VCP)
unnamed: C184.2, U36.5 (VDD18)
unnamed: C203.2, U43.16 (CPI)
unnamed: C203.1, U43.17 (CPO)
unnamed: R113.1, U43.3 (IREF)
unnamed: C204.2, U43.18 (VCP)
unnamed: C214.2, U43.5 (VDD18)
unnamed: C215.2, U44.16 (CPI)
unnamed: C215.1, U44.17 (CPO)
unnamed: R114.1, U44.3 (IREF)
unnamed: C216.2, U44.18 (VCP)
unnamed: C226.2, U44.5 (VDD18)
unnamed: C227.2, U45.16 (CPI)
unnamed: C227.1, U45.17 (CPO)
unnamed: R115.1, U45.3 (IREF)
unnamed: C228.2, U45.18 (VCP)
unnamed: C238.2, U45.5 (VDD18)
TC_MISO: U22.14 (SDO), U23.14 (SDO)
TC_MOSI: U22.11 (SDI), U23.11 (SDI)
TC_SCK: U22.12 (SCLK), U23.12 (SCLK)
VM: C83.1, C84.1, C85.1, C86.1, C87.1, C95.1, C96.1, C97.1, C98.1, C99.1, C107.1, C108.1, C109.1, C110.1, C111.1, C119.1, C120.1, C121.1, C122.1, C123.1, C131.1, C132.1, C133.1, C134.1, C135.1, C143.1, C144.1, C145.1, C146.1, C147.1, C174.1, C175.1, C176.1, C177.1, C178.1, C204.1, C205.1, C206.1, C207.1, C208.1, C216.1, C217.1, C218.1, C219.1, C220.1, C228.1, C229.1, C230.1, C231.1, C232.1, Q3.5 (D), U17.4 (CATHODE), U24.21 (VS), U24.25 (VS), U24.26 (VS), U24.30 (VS), U25.21 (VS), U25.25 (VS), U25.26 (VS), U25.30 (VS), U26.21 (VS), U26.25 (VS), U26.26 (VS), U26.30 (VS), U27.21 (VS), U27.25 (VS), U27.26 (VS), U27.30 (VS), U28.21 (VS), U28.25 (VS), U28.26 (VS), U28.30 (VS), U29.21 (VS), U29.25 (VS), U29.26 (VS), U29.30 (VS), U36.21 (VS), U36.25 (VS), U36.26 (VS), U36.30 (VS), U43.21 (VS), U43.25 (VS), U43.26 (VS), U43.30 (VS), U44.21 (VS), U44.25 (VS), U44.26 (VS), U44.30 (VS), U45.21 (VS), U45.25 (VS), U45.26 (VS), U45.30 (VS)

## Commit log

2026-01-13 Correct kibot actions
2026-01-14 Play around with drivers
2026-01-14 No more eddy, piezo my beloved
2026-01-17 I dont know whats going on here
2026-01-20 Soften scope, begin layout, reorganize sheets (still need to delete extras)
2026-01-27 Regulator decisions
2026-01-27 Notes on ripple + compensation
2026-01-27 loadcell math coming soon(tm)
2026-06-29 Add renovate.json
